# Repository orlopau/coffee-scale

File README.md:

# Coffee-Scale

---

This project contains the schematics, code and 3D models for a coffee scale based on an ESP32.

## Features
* OTA updates via WiFi
* Recipe-based brewing
* Auto averaging of weight values: more values are used to determine weight when weight is relatively constant
* Brew timer
* Lift-to-tare: slide a finger up the side of the platform, lifting it a little, and the scale tares with a double beep. Also with a cup on it, and never during a shot. Off, Gentle, Normal or Firm in the settings.
* USB-C charging
* Interchangeable Load Cell
* 3D-printable case
* Bluetooth and Wi-Fi connectivity

## Recipe-Based Brewing
The scale can be used to brew coffee using a step-by-step recipe. 
The recipe is stored on the scale, and can be adjusted while brewing.

Possible adjustments include:
- Changing the amount of coffee
- Changing the brew ratio
- Other adjustments based on the chosen recipe

## Updates
Once Wi-Fi is set up, the scale looks for a new firmware by itself every few starts, in the background while you weigh. When it finds one, it asks "Update to v1.10?" the next time you switch it on. **Yes** installs it and restarts, **Later** asks again next time. If a new firmware doesn't start properly, the scale goes back to the one before, says so, and doesn't offer that version again.

To update by hand, hold the button while switching on the scale and choose a language.

## Development: Updating From Your Computer
During development, the scale can install a build straight from your computer over Wi-Fi, without USB and without a GitHub release.

1. In `code/`, run `pio run -t serve`. This builds the firmware and serves it on your network. It is found by the scale via mDNS, so your computer's IP does not matter. The first run installs the Python package `zeroconf`.
2. Hold the button while switching on the scale to open the updater. It connects to the Wi-Fi saved in the updater.
3. On the language screen, **long-press** the button instead of clicking. The scale searches for your computer and installs the build. (If it finds no server, it opens the recorder, see below.)

The server keeps running, so for the next build repeat steps 2 and 3 (`pio run -t serve` rebuilds when restarted). If the scale already runs the served build, it shows "No update available". Your computer and the scale must be on the same network, and the firewall must allow incoming connections for the server.

## Development: Trying Automatic Updates
The scale's automatic updates read GitHub's releases. To try them without publishing one, the dev server can pose as a release, and a build can claim to be an older version.

- **Against GitHub:** build with an older version, e.g. `FIRMWARE_VERSION=v1.8.0 pio run -t upload`. The scale then sees the latest release as newer.
- **Against your computer:** run `python scripts/dev_server.py .pio/build/esp32dev/firmware.bin --release v9.9.9 --port 8000` in `code/`. It prints the `RELEASES_URL` to build the scale with, e.g. `RELEASES_URL=http://192.168.1.20:8000/releases pio run -t upload`. Build the firmware to serve with the same `RELEASES_URL`, so it keeps asking your computer. The served build reports the last tag as its version, not `--release`, so after installing it the scale still finds v9.9.9 at every check; build it with `FIRMWARE_VERSION=v9.9.9` too to see the scale stay quiet once it's up to date.

A check runs at the first start of a new firmware if Wi-Fi is set up, then every 5th start; the serial log (`AUTO_UPDATE`) says when.

## Development: Recording the Load Cell
The scale can record the raw readings of its load cell, e.g. of taps or an espresso shot, and save them in its flash. The recordings are test data: native tests replay them with `RecordedScale` (`code/src/native/recorded_scale.h`). You don't need your computer while recording.

1. Install a build with the recorder on the scale, see above.
2. Open the updater and long-press on the language screen, as for an update. If no server is found, the scale opens the recorder by itself. It shows how many recordings are saved, and "No server".

**Click** to start a recording. While recording, the scale shows the weight, the recording time, the time left and the number of markers. **Click** again to set a marker, e.g. when the pump starts. **Turn** the knob to tare the shown weight, e.g. after putting the cup on; while recording, the tare is saved in the recording too. **Long-press** to save the recording in the scale's flash; the scale then waits for the click that starts the next one. A recording takes at most 5 minutes, then the scale waits for the long-press. About 50 recordings fit. If saving fails, the recording is kept and the next long-press tries again. A recording that wasn't saved is lost when the scale is switched off.

To get the recordings to your computer, run `pio run -t record` in `code/`. It does not build anything, it waits for recordings. Only one of `serve` and `record` can run at a time. Open the recorder as above; the scale now finds the server and no longer says "No server". **Long-press** while idle to send all saved recordings, oldest first. Each one is deleted from the scale after it arrived, so if sending fails, the rest stays and the next long-press tries again.

The computer saves each recording as `code/test/recordings/<date>_<time>.csv`. Give the useful ones a name that says what they show, commit them, and delete the rest. A recording looks like this, with `ms` counted from its start on the scale's clock:

```
# coffee-scale recording
# firmware: v1.9.0
# grams_per_count: 0.002381
ms,event,value
0,sample,84012
101,sample,84020
1234,click,
1500,tare,
```

`grams_per_count` is the calibration of the scale that recorded, so tests can convert the raw readings to grams. A sample's `value` is the HX711's raw reading, signed. The samples stay raw after a tare, a `tare` row only says when it happened (`RecordedScale::tares()`). Firmware up to v1.9.0 recorded it unsigned (16540413 instead of -236803), and the replay converts those.

## Development: Emulator
The emulator runs the firmware on your computer, in a window that shows the scale's display. It needs SDL2 (`sudo apt install libsdl2-dev` on Debian/Ubuntu).

```
cd code
pio run -e emulator -t exec
```

With `COMPILE_LANG=de` in front, it runs in German. The load cell is simulated, and the keyboard replaces the encoder:

| Key | Action |
|---|---|
| Left / Right | turn the encoder |
| Enter, Space | press the encoder, hold for a long press |
| Up / Down | put 1 g on the scale or take it off, with Shift 0.1 g |
| PageUp / PageDown | 10 g on or off |
| Home | 100 g, e.g. for the calibration |
| 0, Backspace | clear the scale |
| F | pour on/off, 2 g/s |
| S | espresso shot: 6 s pre-infusion, then about 38 g in 33 s |
| L | lift the platform for a moment (lift-to-tare) |
| N | noise on/off |
| - / + | slower/faster time, up to 20x (1x while the button is held) |
| P | save a screenshot to the current directory |
| Esc, Q | quit |

The window title shows the weight on the scale. The frame around the display lights up while the buzzer sounds. Settings are kept in memory only, and the boot splash screen and the updater only run on the device.

## Development: Screenshot Tests
The native tests render every screen through u8g2, set up like the scale's display, and compare it with the reference images in `code/test/native/test_screenshots/screens/`. A screen that changes fails the tests, and its new image is written to `code/test/native/test_screenshots/failed/` (on GitHub, attached to the CI run as `failed-screenshots`).

After changing a screen on purpose, accept the new images and commit them with the change:

```
cd code
UPDATE_SCREENSHOTS=1 pio test -e native -f native/test_screenshots
```

The diff of the pull request then shows each changed screen before and after.

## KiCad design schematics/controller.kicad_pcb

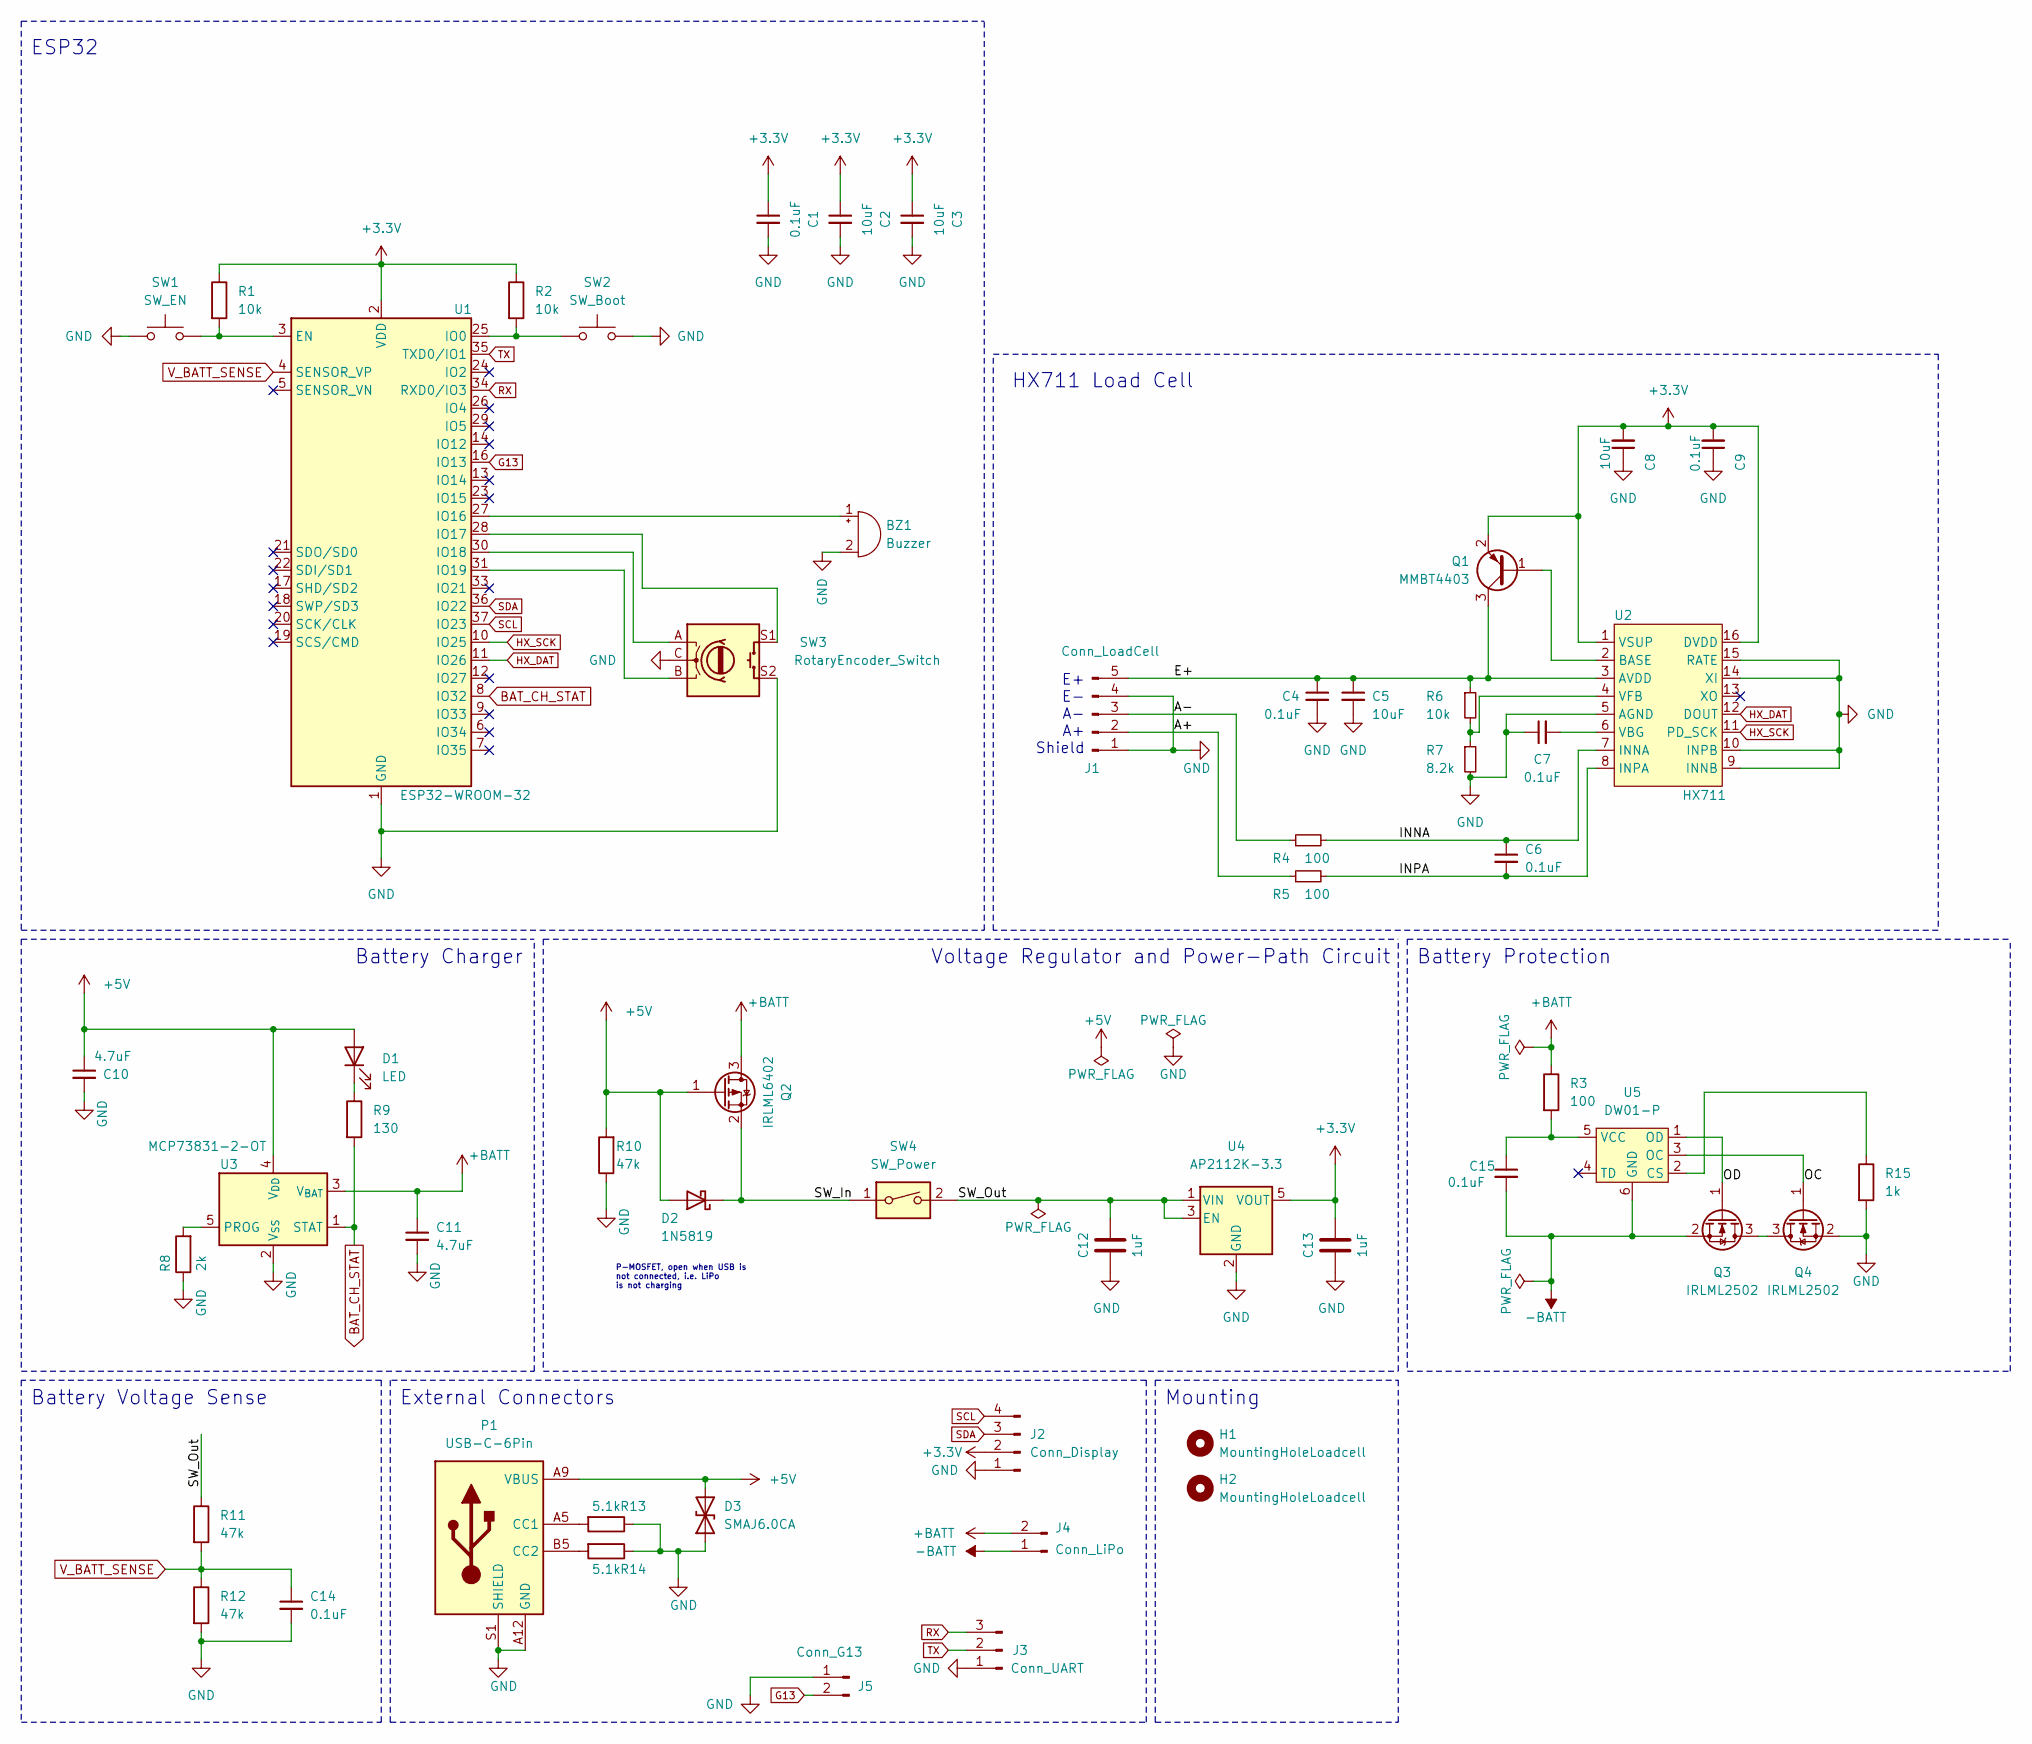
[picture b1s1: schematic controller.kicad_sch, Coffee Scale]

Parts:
BZ1: Buzzer; Buzzer_12x9.5RM7.6
C1, C4, C6, C7, C9, C14, C15: 0.1uF; C_0603_1608Metric_Pad1.08x0.95mm_HandSolder; LCSC C14663
C2, C3, C5, C8: 10uF; C_1206_3216Metric; LCSC C13585
C10, C11: 4.7uF; C_0805_2012Metric; LCSC C1779
C12, C13: 1uF; C_0805_2012Metric; LCSC C28323
D1: LED; LED_1206_3216Metric; LCSC C125086
D2: 1N5819; D_SMA_Handsoldering
D3: SMAJ6.0CA; D_SMA
H1, H2: MountingHoleLoadcell; MountingHole_5.3mm_M5_ISO7380
J1: Conn_LoadCell; SolderWire-0.5sqmm_1x05_P4.8mm_D0.9mm_OD2.3mm
J2: Conn_Display; SolderWire-0.5sqmm_1x04_P4.8mm_D0.9mm_OD2.3mm
J3: Conn_UART; PinHeader_1x03_P2.54mm_Horizontal
J4: Conn_LiPo; SolderWire-0.5sqmm_1x02_P4.8mm_D0.9mm_OD2.3mm
J5: Conn_G13; SolderWire-0.5sqmm_1x02_P4.8mm_D0.9mm_OD2.3mm
P1: USB-C-6Pin; USB_C_6Pin
Q1: MMBT4403; SOT-23; LCSC C78864
Q2: IRLML6402; SOT-23; LCSC C2593
Q3, Q4: IRLML2502; SOT-23; LCSC C5364308
R1, R2, R6: 10k; R_0603_1608Metric_Pad0.98x0.95mm_HandSolder; LCSC C25804
R3, R4, R5: 100; R_0603_1608Metric_Pad0.98x0.95mm_HandSolder; LCSC C22775
R7: 8.2k; R_0603_1608Metric_Pad0.98x0.95mm_HandSolder; LCSC C25981
R8: 2k; R_0603_1608Metric_Pad0.98x0.95mm_HandSolder; LCSC C22975
R9: 130; R_0603_1608Metric_Pad0.98x0.95mm_HandSolder; LCSC C22808
R10, R11, R12: 47k; R_0603_1608Metric_Pad0.98x0.95mm_HandSolder; LCSC C25819
R13, R14: 5.1k; R_0603_1608Metric_Pad0.98x0.95mm_HandSolder; LCSC C23186
R15: 1k; R_0603_1608Metric_Pad0.98x0.95mm_HandSolder; LCSC C21190
SW1: SW_EN; SW_PUSH_6mm_H5mm
SW2: SW_Boot; SW_PUSH_6mm_H5mm
SW3: RotaryEncoder_Switch; RotaryEncoder_Alps_EC11E-Switch_Vertical_H20mm
SW4: SW_Power; SolderWire-0.5sqmm_1x02_P4.8mm_D0.9mm_OD2.3mm
U1: ESP32-WROOM-32; LCSC C473012
U2: HX711; SOP-16_3.9x9.9mm_P1.27mm; LCSC C6705483
U3: MCP73831-2-OT; SOT-23-5; LCSC C424093
U4: AP2112K-3.3; SOT-23-5; LCSC C51118
U5: DW01-P; SOT-23-6_Handsoldering; LCSC C18164398

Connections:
+3.3V: C1.1, C2.1, C3.1, C8.2, C9.2, C13.2, J2.2, Q1.2 (E), R1.1, R2.1, U1.2 (VDD), U2.1 (VSUP), U2.16 (DVDD), U4.5 (VOUT)
+5V: C10.1, D1.2 (A), D2.2 (A), D3.2 (A2), P1.A9 (VBUS), P1.B9 (VBUS), Q2.1 (G), R10.2, U3.4 (V_{DD})
+BATT: C11.1, J4.2, Q2.3 (D), R3.1, U3.3 (V_{BAT})
-BATT: C15.2, J4.1, Q3.2 (S), U5.6 (GND)
/E+: C4.1, C5.1, J1.5, Q1.3 (C), R6.1, U2.3 (AVDD)
/INNA: C6.1, R4.2, U2.7 (INNA)
/INPA: C6.2, R5.2, U2.8 (INPA)
/OC: Q4.1 (G), U5.3 (OC)
/OD: Q3.1 (G), U5.1 (OD)
/SW_In: D2.1 (K), Q2.2 (S), SW4.1
/SW_Out: C12.2, R11.1, SW4.2, U4.1 (VIN), U4.3 (EN)
BAT_CH_STAT: R9.2, U1.8 (IO32), U3.1 (STAT)
G13: J5.2, U1.16 (IO13)
HX_DAT: U1.11 (IO26), U2.12 (DOUT)
HX_SCK: U1.10 (IO25), U2.11 (PD_SCK)
unnamed: BZ1.1 (+), U1.27 (IO16)
unnamed: D1.1 (K), R9.1
unnamed: P1.A5 (CC1), R13.2
unnamed: P1.B5 (CC2), R14.2
unnamed: Q1.1 (B), U2.2 (BASE)
unnamed: Q3.3 (D), Q4.3 (D)
unnamed: R1.2, SW1.2, U1.3 (EN)
unnamed: R2.2, SW2.1, U1.25 (IO0)
unnamed: SW3.S1, U1.28 (IO17)
unnamed: SW3.A, U1.30 (IO18)
unnamed: SW3.B, U1.31 (IO19)
unnamed: C7.2, U2.6 (VBG)
unnamed: R6.2, R7.1, U2.4 (VFB)
unnamed: R8.2, U3.5 (PROG)
unnamed: R15.1, U5.2 (CS)
unnamed: C15.1, R3.2, U5.5 (VCC)
RX: J3.3, U1.34 (RXD0/IO3)
SCL: J2.4, U1.37 (IO23)
SDA: J2.3, U1.36 (IO22)
TX: J3.2, U1.35 (TXD0/IO1)
V_BATT_SENSE: C14.1, R11.2, R12.1, U1.4 (SENSOR_VP)

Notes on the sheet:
ESP32
Battery Charger
HX711 Load Cell
E+ E- A- A+ Shield
Battery Protection
Mounting
External Connectors
Battery Voltage Sense
Voltage Regulator and Power-Path Circuit
P-MOSFET, open when USB is not connected, i.e. LiPo is not charging

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
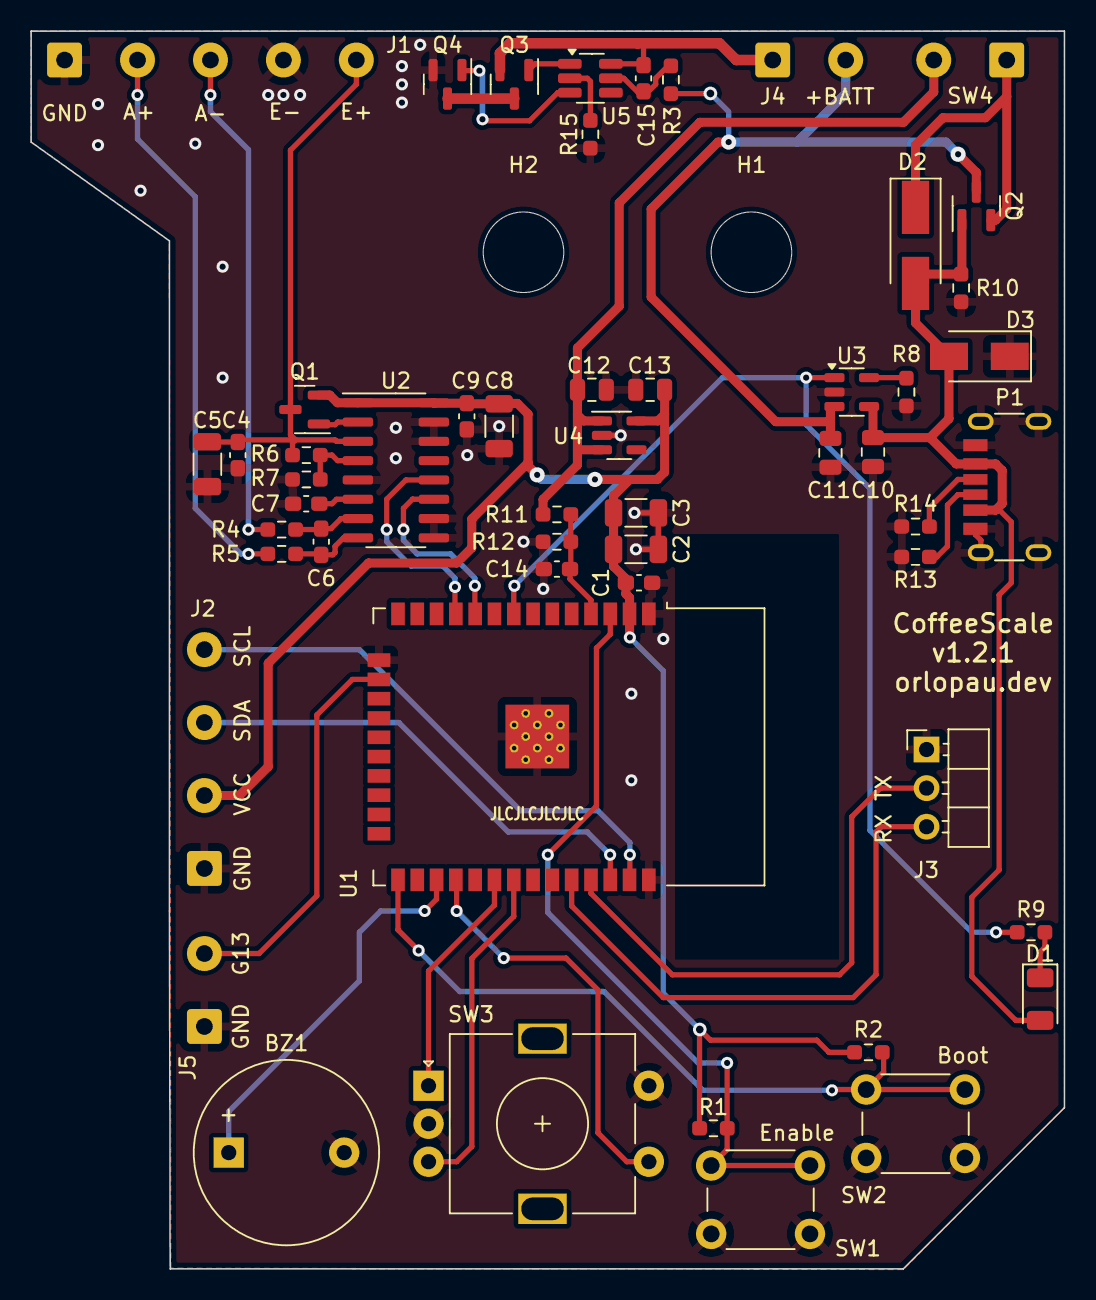
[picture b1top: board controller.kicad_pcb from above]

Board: 2 copper layers, 68.0 x 81.5 mm, 55 parts (0 on the bottom side), 39 nets.

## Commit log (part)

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2022-11-02 Added pcb design
2022-11-07 Updated pcb
2022-11-10 Added initial code
2022-11-22 Added code for embedded and native, plus tests
    Temp
2022-11-22 Added button to click type converter
2022-11-22 Added tests for battery measurement
2022-11-22 Added rotary encoder support
2022-11-23 Added calibration mode
2022-11-24 Added mode manager
2022-11-26 Added native recipe mode and tests
2022-11-26 Fixed tests for mode manager and mode default
2022-11-26 Added github action for platformio unit tests
2022-11-26 Added selection mode to display
2022-11-27 Began calibration, todo
2022-12-01 Began work on hx711 driver
2022-12-01 Removed duplicate calibration mode
2022-12-01 Reworked mode switcher
2022-12-01 Fixed segfault, missing null termiantion
2022-12-01 Fixed mode manager
    Mode manager called the update function of the next chosen mode in the same tick.
    This lead to the single click which is needed to select a new mode being propagated
    instantly to the new mode.
2022-12-02 Added methods for recipe displaying to u8g2 display implementation
2022-12-02 Updated voltage divider for hx711 in schematic
2022-12-02 Added screen on scale startup
2022-12-03 Fixed scale scaling
2022-12-06 Refactored recipe configuration step
2022-12-06 Fixed ratio of pours not being adjusted
2022-12-06 Centered text for mode switcher
2022-12-06 Added battery state to mode switcher screen
2022-12-06 Fixed test for loadcell tare
    Was not adjusted to taring via rotating the encoder
2022-12-06 Added 5-Pour recipe
2022-12-06 Changed unsigned int to int for remaining weight in a pour
2022-12-06 Added extra display method for recipe prepare step
2022-12-06 Added readme
2022-12-06 Added buzzer tone function
2022-12-06 Added buzzer tone to mode recipes
2022-12-07 Refactored load cell into WeightSensor which uses a LoadCell
2022-12-07 Added ring buffer
2022-12-08 Added relative methods to ring buffer
2022-12-08 Added auto averagiung to loadcell implementation
2022-12-14 Updated schematic to v1.1.0
    * Added TVS diode for USB connector
    * Added active buzzer instead of passive piezo buzzer
    * Added battery protection IC
    * Changed location of enable button, enabling the mounting of a button which is visible externally
2022-12-14 Changed circular mounting holes to eliptical for rotary encoder
2022-12-16 Added automatic font file generation based on ttf files for u8g2 library
2022-12-16 Reworked config screens
2022-12-16 Updated switchher design
2022-12-20 Refactored steps into own files
2022-12-20 Added clang format file
2022-12-20 Refactored step tests into own test cases
2022-12-21 Added auto advance feature for pours
2022-12-21 Added auto start feature for pours
2022-12-21 Adjusted auto advance and auto start for aeropress recipe
2022-12-21 Fixed pause time not being shown when pour time is zero
    When autoStart was not disabled for a pour, and the
    pourTime for that pour was 0, 0 would be displayed instead
    of the pauseTime.
2022-12-21 Removed brew state enum
2022-12-27 Fixed wrong scaling for ADC values
2022-12-27 Fixed missing include in ring buffer
2022-12-27 Removed ratio from recipe struct
2022-12-27 Removed ratio from actual recipes
2022-12-27 Fixed divider in u8g display for ratios
2022-12-27 Fixed brewing step showing only the weight of the current pour
2022-12-27 Fixed double negative signs in pouring weight screen.
    Closes #16
2023-01-05 Fixed calibration mode
2023-01-05 Fixed unstable debounce test
2023-01-09 Added OTA updates with captive portal for WiFi connections
2023-01-09 Added continous deployment
2023-01-09 Fixed tests by introducing guards for native
2023-01-09 Fixed deployment actions
2023-01-09 Fixed update not using HTTPS
2023-01-09 Fixed calibration not waiting for laodcell readiness
2023-01-09 Added badges to readme
2023-01-09 Added long click detection when button is kept pressed
    Previously for detecting a long click the button must have been released.
2023-01-09 Added tare to brewing step on rotary encoder rotation
2023-01-09 Changed partition table to use 16MB
2023-01-10 Fixed flickering battery display by introducing an update interval
2023-01-10 Changed serial prints to use esp32 logger
2023-01-10 Improved initial tare by averaging over multiple samples
2023-01-10 Fixed missing dependency in native logger
2023-01-10 Added automatically wrapping text for display
2023-01-10 Added original V60 recipe
2023-01-10 Fixed voltage not showing when internal millis was less than interval
2023-01-10 Added automatic version define based on latest firmware-* tag
2023-01-10 Fixed deployment script did not fetch tags
2023-01-11 Added recipe for french press
2023-01-11 Added qr code
2023-01-11 Increased battery update interval
2023-01-13 Added localization for recipes
2023-01-15 Added localization for update and added UTF8 support
2023-01-15 Modified deployment action to build both firmwares
2023-01-15 Added language choice to update mechanism
2023-01-21 Fixed deploy workflow
2023-01-29 Refactored mode default to mode scale
2023-01-29 Added least squares regression
2023-01-29 Added espresso mode
2023-04-03 Fixed a bug when setting a new ratio, advancing to the weight config step and then returning.
    In this case the ratio was not reset correctly.
    Closes #25.
2023-05-06 Added 3D models for sclae
2023-05-06 Feature: User can force progress a pour, even when it has not finished
    Fixed #24
2023-05-06 Feature: Added auto advance for V60 Kasuya recipe
2023-05-06 Feature: Added calibration printout, scale can now be negative
2023-05-06 Bugfix: Auto averaging did not work with negative scales
2023-11-26 Added *.step models for scale and knob
2023-12-02 Added freertos tasks
2023-12-02 Added util directory
2024-12-05 Changed lipo protection IC to DW01, added LCSC part numbers
2024-12-08 Separated user interface and display headers, made interface not be a class
2024-12-08 Refactored loadcell and battery to not be classes anymore
2024-12-08 Re-enabled test
2024-12-10 wip display to namespace need to fix display mock
2024-12-14 Changed display to be a namespace
2024-12-14 Renamed scale.h to weight_sensor.h
2024-12-14 Added auto tare to scale, doesnt do anything yet as there is no config for known weights
2024-12-14 Added functioning auto tare with customisable settings
2024-12-14 Added config parameter for auto tare tolerance
2025-02-07 Added customizable auto tare threshold
2025-02-07 wip docs
